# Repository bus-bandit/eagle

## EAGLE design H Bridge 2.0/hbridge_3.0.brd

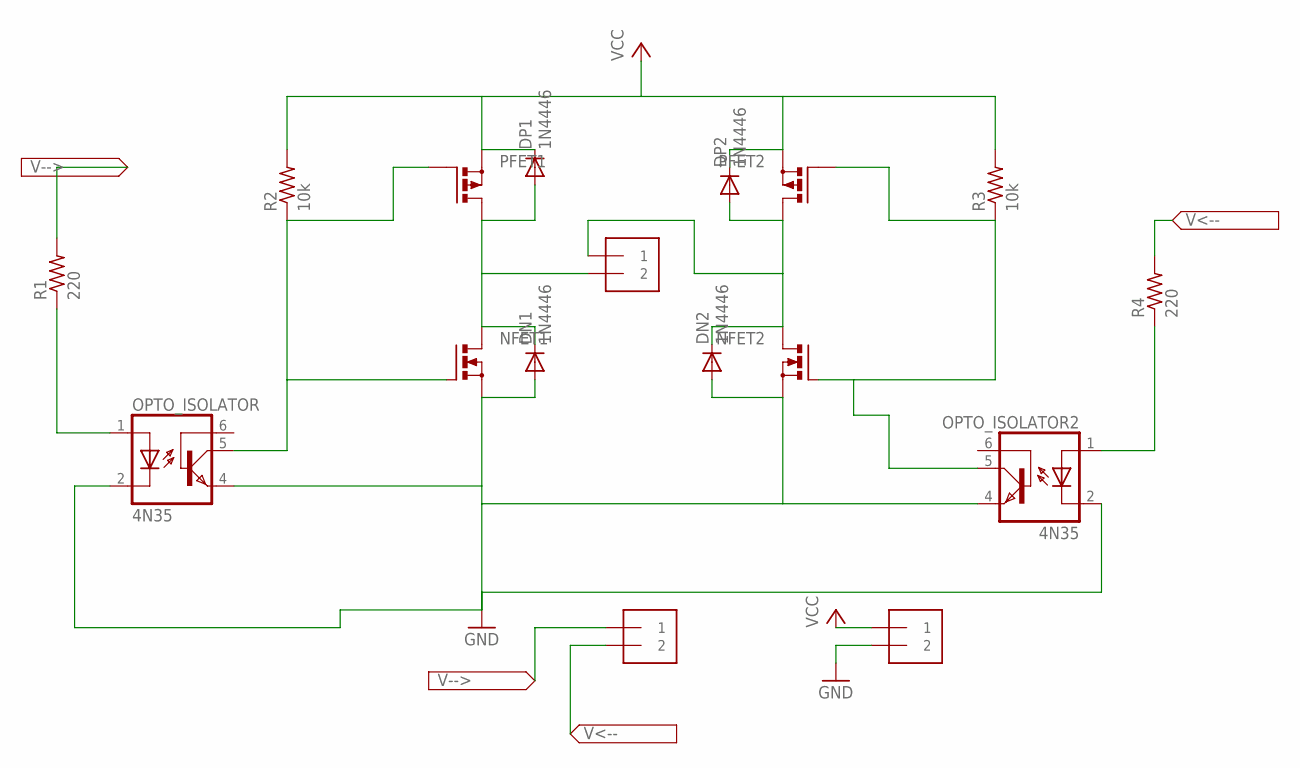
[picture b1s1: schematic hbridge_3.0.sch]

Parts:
ARDUINO: 1X2-3.5MM
DN1, DN2: 1N4446; DO35-10
DP1, DP2: 1N4446; DO35-10
MOTOR: 1X2-3.5MM
NFET1, NFET2: PMOSFET_NTO220BH; TO220BH
OPTO_ISOLATOR, OPTO_ISOLATOR2: 4N35; DIL06
PFET1, PFET2: PMOSFET_PTO220BH; TO220BH
POWER: 1X2-3.5MM
R1, R4: 220; 0207/15
R2, R3: 10k; 0207/15

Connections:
ARDUINO_A: ARDUINO.1, R1.2
ARDUINO_B: ARDUINO.2, R4.2
GND: DN1.A, DN2.A, NFET1.S, NFET2.S, OPTO_ISOLATOR.2 (C), OPTO_ISOLATOR.4 (EMI), OPTO_ISOLATOR2.2 (C), OPTO_ISOLATOR2.4 (EMI), POWER.2
MOTOR1: DN2.C, DP2.A, MOTOR.1, NFET2.D, PFET2.D
MOTOR2: DN1.C, DP1.A, MOTOR.2, NFET1.D, PFET1.D
unnamed: OPTO_ISOLATOR.1 (A), R1.1
unnamed: OPTO_ISOLATOR2.1 (A), R4.1
OPTO1: NFET1.G, OPTO_ISOLATOR.5 (COL), PFET1.G, R2.1
OPTO2: NFET2.G, OPTO_ISOLATOR2.5 (COL), PFET2.G, R3.1
VCC: DP1.C, DP2.C, PFET1.S, PFET2.S, POWER.1, R2.2, R3.2

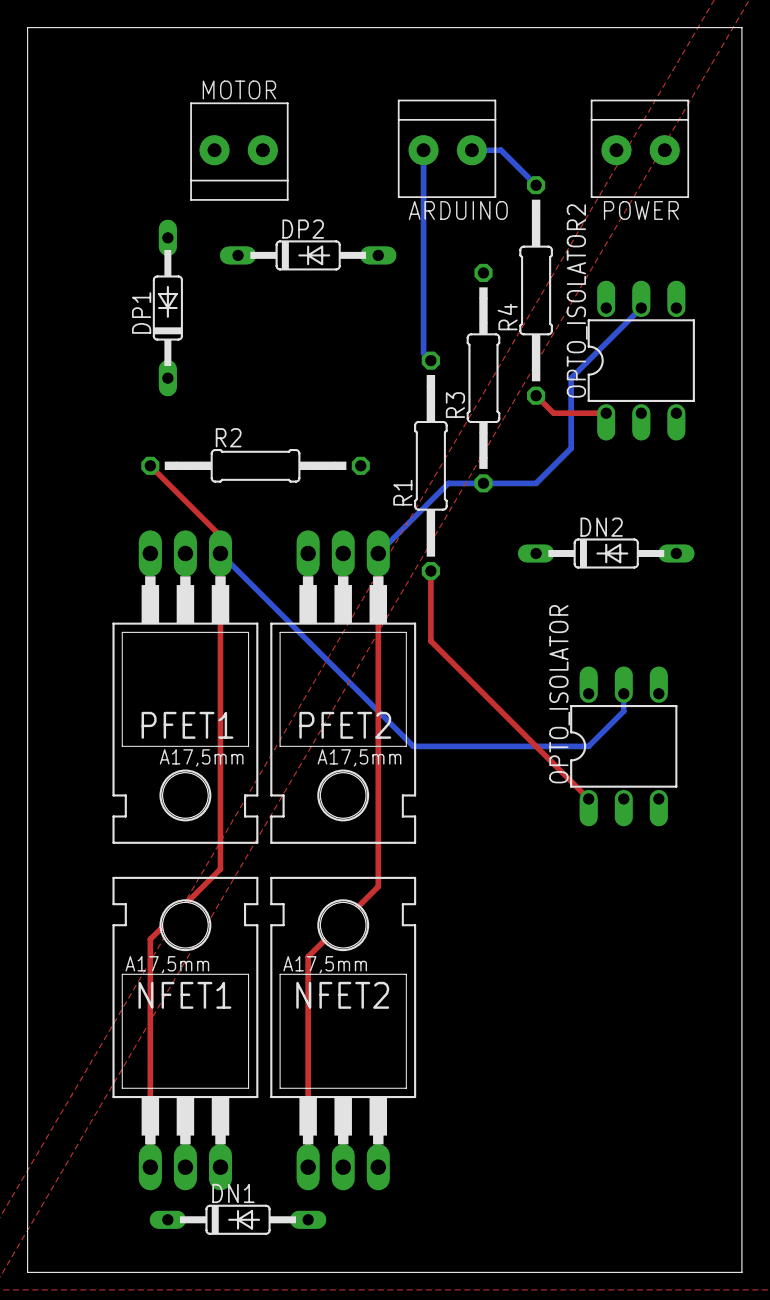
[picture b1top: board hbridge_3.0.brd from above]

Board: 2 copper layers, 51.7 x 90.2 mm, 17 parts (0 on the bottom side), 10 nets.

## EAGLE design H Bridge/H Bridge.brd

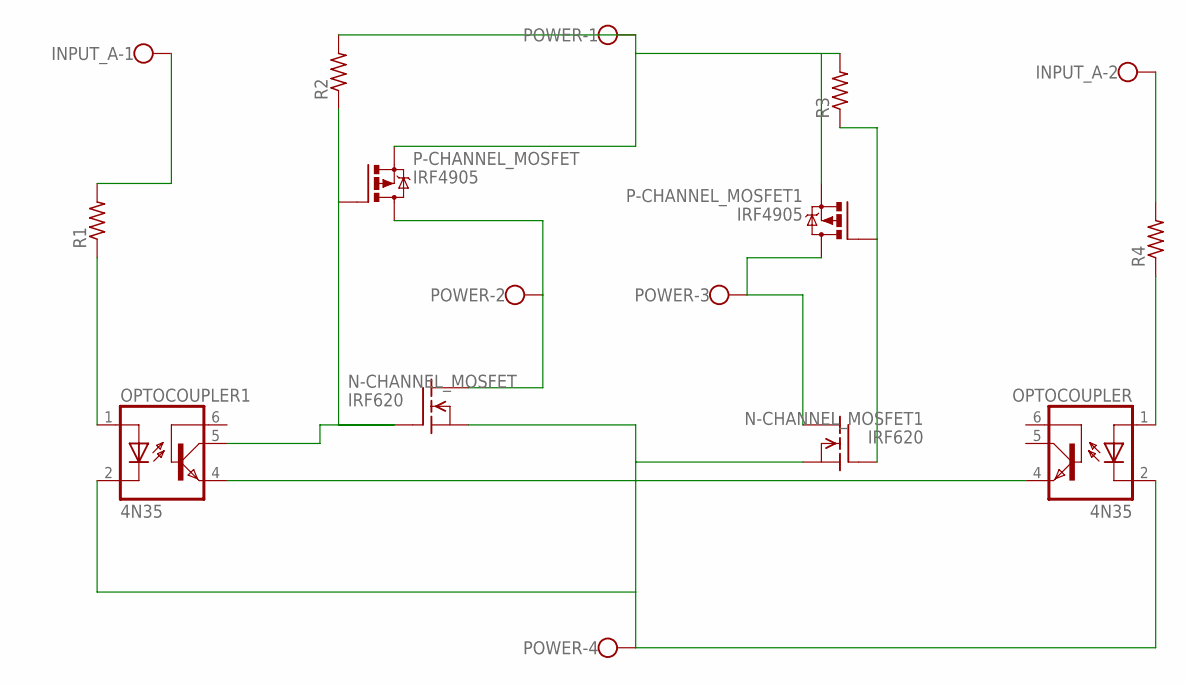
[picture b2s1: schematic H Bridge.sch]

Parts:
INPUT_A: W237-4
N-CHANNEL_MOSFET, N-CHANNEL_MOSFET1: IRF620; TO220
OPTOCOUPLER, OPTOCOUPLER1: 4N35; DIL06
P-CHANNEL_MOSFET, P-CHANNEL_MOSFET1: IRF4905; TO220BH
POWER: W237-4
R1, R2, R3, R4: R-US_0207/10; 0207/10

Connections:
unnamed: P-CHANNEL_MOSFET.S, P-CHANNEL_MOSFET1.S, POWER.1, R2.2, R3.2
unnamed: N-CHANNEL_MOSFET.1 (G), OPTOCOUPLER1.5 (COL), P-CHANNEL_MOSFET.G, R2.1
unnamed: N-CHANNEL_MOSFET.3 (S), N-CHANNEL_MOSFET1.3 (S), OPTOCOUPLER.2 (C), OPTOCOUPLER.4 (EMI), OPTOCOUPLER1.2 (C), OPTOCOUPLER1.4 (EMI), POWER.4
unnamed: N-CHANNEL_MOSFET1.1 (G), P-CHANNEL_MOSFET1.G, R3.1
unnamed: N-CHANNEL_MOSFET1.2 (D), P-CHANNEL_MOSFET1.D, POWER.3
unnamed: N-CHANNEL_MOSFET.2 (D), P-CHANNEL_MOSFET.D, POWER.2
unnamed: OPTOCOUPLER1.1 (A), R1.1
unnamed: INPUT_A.1, R1.2
unnamed: INPUT_A.2, R4.2
unnamed: OPTOCOUPLER.1 (A), R4.1

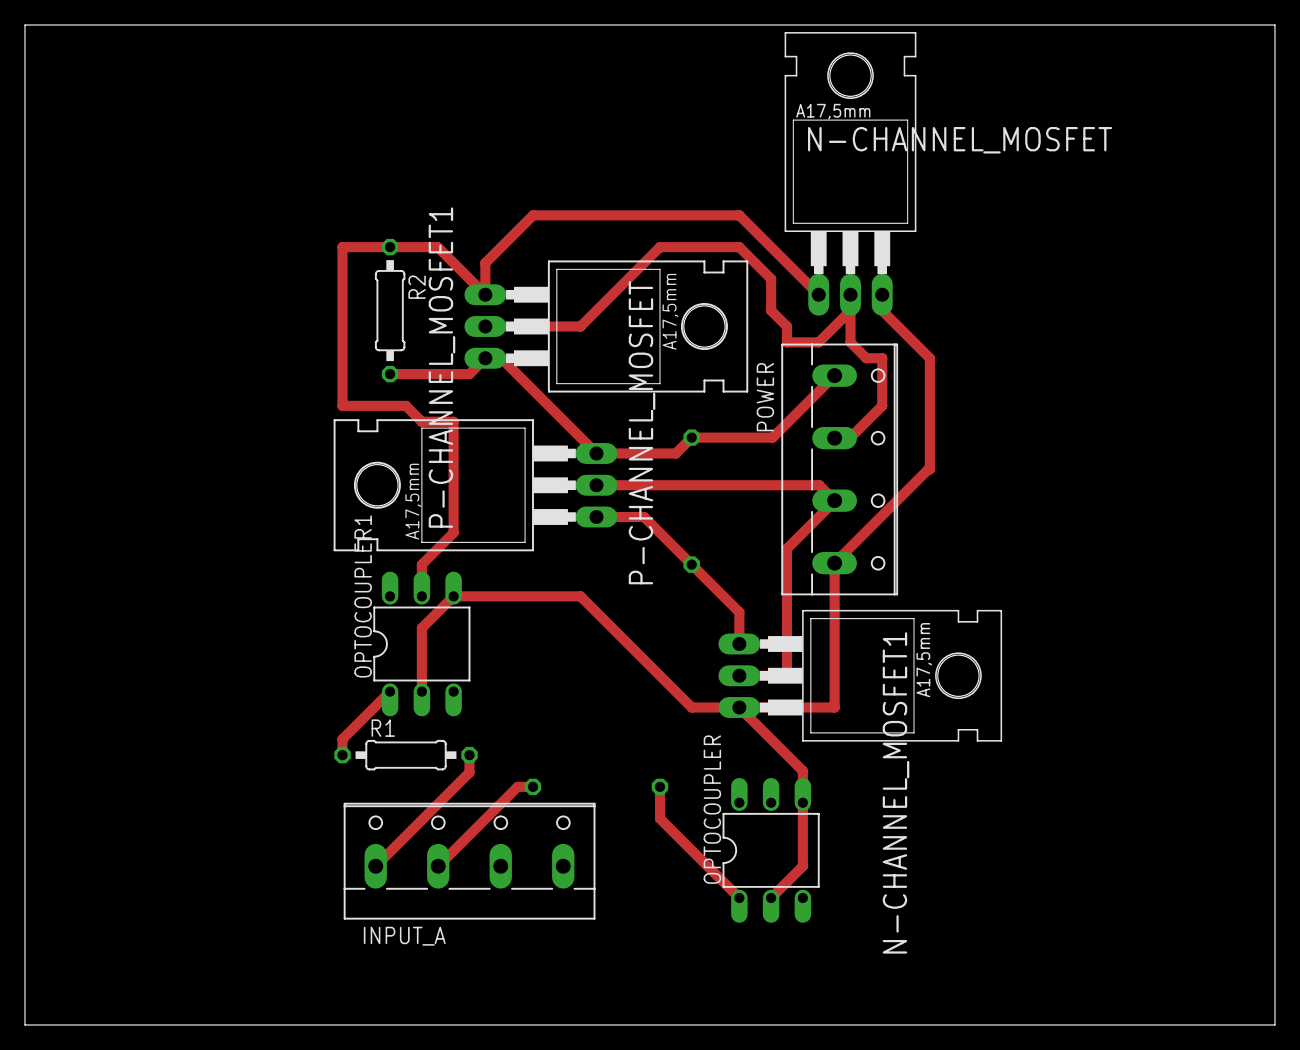
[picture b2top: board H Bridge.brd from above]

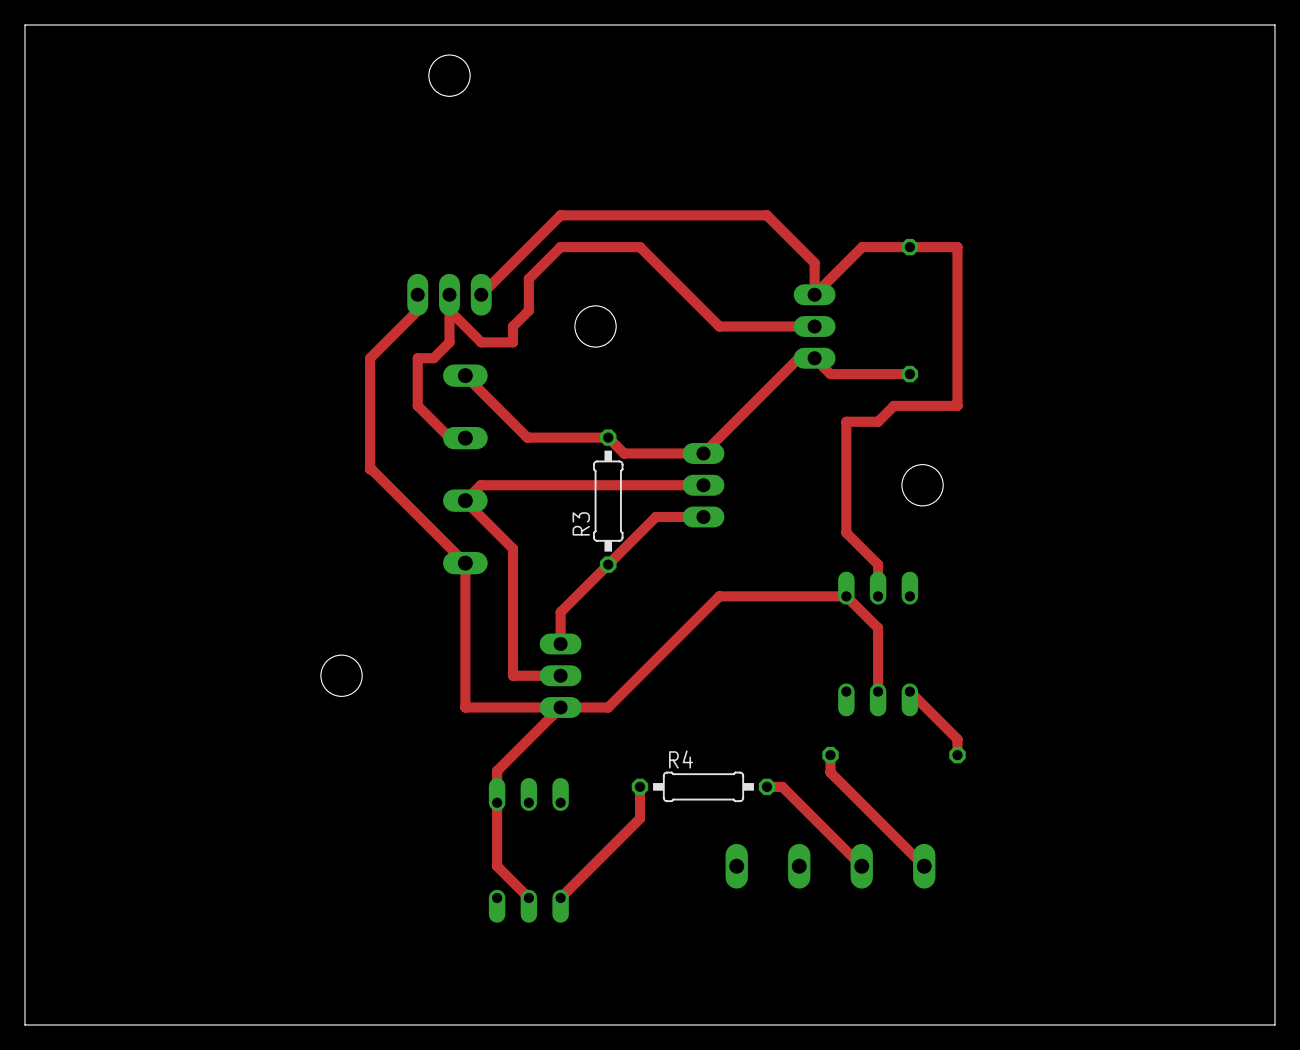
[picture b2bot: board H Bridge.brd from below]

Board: 2 copper layers, 100.0 x 80.0 mm, 12 parts (2 on the bottom side), 10 nets.

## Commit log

2016-11-19 :space_invader: Added .gitattributes & .gitignore files
2016-11-19 added h bridge boards
2016-11-20 routing and organizing
